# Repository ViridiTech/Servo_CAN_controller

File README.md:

# Servo_CAN_controller
Board allowing to turn DC motors into servomechanisms controlled by CAN bus using ESP32-C3 chip and AS5600 magnetic encoder

</a>

This is the first version of ESP32-C3 microcontroller board with CAN transciever, DC motor driver (DRV8838) and magnetic encoder (AS5600). I will use it to control custom linear actuator.

# PCB layout
</a>
</a>

Top side has USB-C port, ESP32-C3FH4 chip, 40MHz crystal oscillator, CAN transciever module, 3.3V voltage regulator, DRV8838 DC motor driver and all passive components. Bottom side consists of breakout pads for power, ground and CAN lines and AS5600 magnetic ennoder

# Disclaimer
This board is yet to be assembled and tested.

I welcome you to discussion!

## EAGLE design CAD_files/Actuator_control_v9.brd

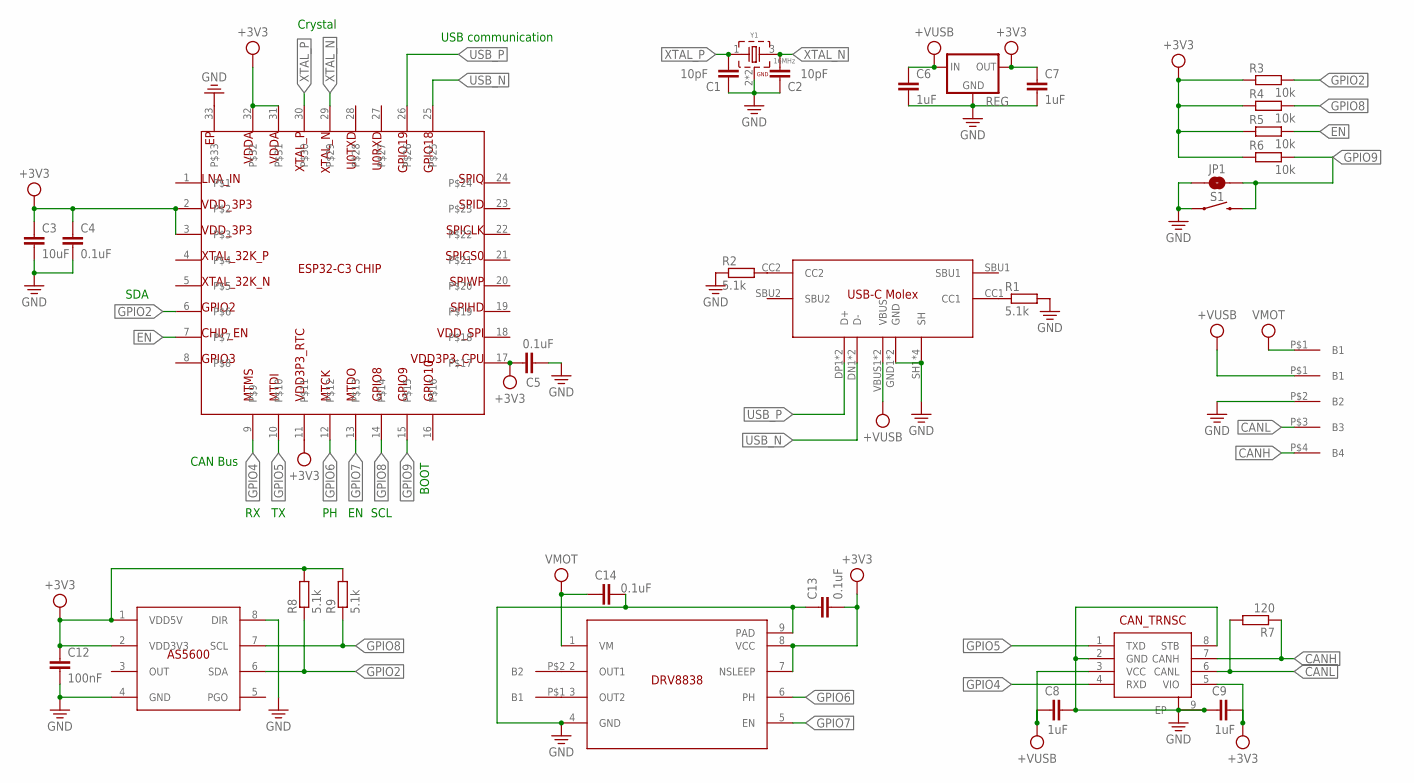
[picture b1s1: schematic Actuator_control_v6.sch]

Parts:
AS5600: AS5600; SOIC127P600X175-8N
C1, C2: 10pF; C0402
C3: 10uF; C0402
C4, C5, C13, C14: 0.1uF; C0402
C6, C7, C8, C9: 1uF; C0402
C12: 100nF; C0402
CAN: CAN_TRNSC; SON65P300X300X75-9T160X240N
DRV8838: DRV8838; SON50P200X200X80-9T90X160N
ESP32: ESP32-C3CHIP; ESP32-C3_CHIP
JP1: JUMPER-SMT_2_NO_SILK; SMT-JUMPER_2_NO_SILK
R1, R2, R8, R9: 5.1k; R0402
R3, R4, R5, R6: 10k; R0402
R7: 120; R0402
REG: XC63FPM; SOT23
S1: MOMENTARY-SWITCH-SPST-SMD-6.0X3.5MM; TACTILE_SWITCH_SMD_6.0X3.5MM
U$3: USB-CMOLEX
U$6: BREAKOUT_44-SMD2.54; BREAKOUT_4_SMD_2.54
U$7: BREAKOUT_11-SMD-2.54; BREAKOUT_1_SMD_2.54
U$8: BREAKOUT_22-THT; BREAKOUT_2_THT
Y1: 16MHz; WE-XTAL_CFPX-180

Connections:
+3V3: AS5600.1 (VDD5V), AS5600.2 (VDD3V3), C3.1, C4.1, C5.2, C7.1, C9.2, C12.1, C13.2, CAN.5 (VIO), DRV8838.7 (NSLEEP), DRV8838.8 (VCC), ESP32.2, ESP32.3, ESP32.11, ESP32.17, ESP32.31, ESP32.32, R3.1, R4.1, R5.1, R6.2, R8.2, R9.2, REG.2 (OUT)
+VUSB: C6.1, C8.1, CAN.3 (VCC), REG.3 (IN), U$3.VBUS1 (VBUS), U$3.VBUS2 (VBUS), U$6.P$1 (B1)
CANH: CAN.7 (CANH), R7.1, U$6.P$4 (B4)
CANL: CAN.6 (CANL), R7.2, U$6.P$3 (B3)
EN: ESP32.7, R5.2
GND: AS5600.4 (GND), AS5600.8 (DIR), C1.1, C2.1, C3.2, C4.2, C5.1, C6.2, C7.2, C8.2, C9.1, C12.2, C13.1, C14.2, CAN.2 (GND), CAN.8 (STB), CAN.9 (EP), DRV8838.4 (GND), DRV8838.9 (PAD), ESP32.33, JP1.1, R1.2, R2.1, REG.1 (GND), S1.1, U$3.GND1 (GND), U$3.GND2 (GND), U$3.SH1 (SH), U$3.SH2 (SH), U$3.SH3 (SH), U$3.SH4 (SH), U$6.P$2 (B2), Y1.2 (GND), Y1.4 (GND)
GPIO2: AS5600.6 (SDA), ESP32.6, R3.2, R8.1
GPIO4: CAN.4 (RXD), ESP32.9
GPIO5: CAN.1 (TXD), ESP32.10
GPIO6: DRV8838.6 (PH), ESP32.12
GPIO7: DRV8838.5 (EN), ESP32.13
GPIO8: AS5600.7 (SCL), ESP32.14, R4.2, R9.1
GPIO9: ESP32.15, JP1.2, R6.1, S1.2
unnamed: R1.1, U$3.CC1
unnamed: R2.2, U$3.CC2
unnamed: DRV8838.3 (OUT2), U$8.P$1 (B1)
unnamed: DRV8838.2 (OUT1), U$8.P$2 (B2)
OUT: AS5600.3 (OUT)
PGO: AS5600.5 (PGO)
USB_N: ESP32.25, U$3.DN1 (D-), U$3.DN2 (D-)
USB_P: ESP32.26, U$3.DP1 (D+), U$3.DP2 (D+)
VMOT: C14.1, DRV8838.1 (VM), U$7.P$1
XTAL_N: C2.2, ESP32.29, Y1.3 (2)
XTAL_P: C1.2, ESP32.30, Y1.1

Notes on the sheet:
USB communication
Crystal
CAN Bus
SCL
SDA
BOOT

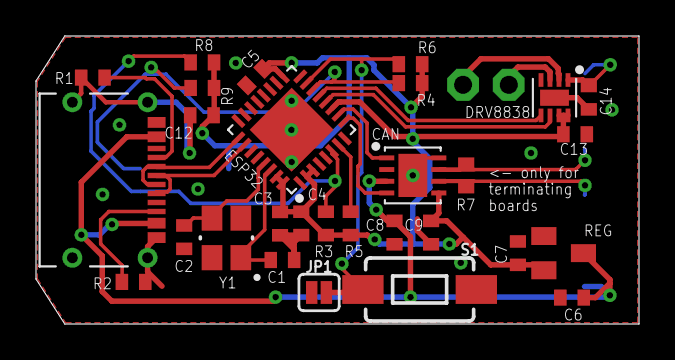
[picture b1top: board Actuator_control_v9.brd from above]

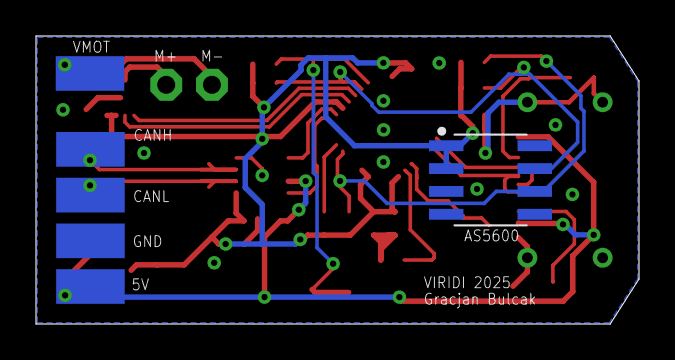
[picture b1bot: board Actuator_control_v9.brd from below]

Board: 2 copper layers, 33.5 x 16.0 mm, 33 parts (3 on the bottom side), 22 nets.

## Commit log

2025-02-16 renaming files
2025-02-16 Rename Actuator control v6.pdf to Schematic v6.pdf
2025-02-16 Added CAD files
2025-02-17 File ordering & BOM added
2025-03-07 Updated board
    Fixed Issue #8 "R1 is floating, not connected to GND"
2025-03-08 Resolved issue #9
    Removed CAN lines capacitors and added info regarding terminating resistors
2025-03-09 .STEP update

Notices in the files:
parts and their libraries:
Wurth_Quartz Crystals: Copyright: Würth Elektronik
SparkFun-Jumpers: Licensing: Creative Commons ShareAlike 4.0 International - https://creativecommons.org/licenses/by-sa/4.0
